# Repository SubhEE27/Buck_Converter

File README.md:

# LMR51450 Based Buck Converter (10–35 V → 7.6 V @ 4 A)

This project implements a **DC-DC Buck Converter** using the **Texas Instruments LMR51450** regulator IC.  
The design converts an input range of **10 V to 35 V** into a regulated **7.6 V output** at up to **4 A continuous current**.

The schematic, PCB layout, and BOM are included, designed in **KiCad**.

---

## 📐 Design Specifications
- Input Voltage Range: 10 – 35 V  
- Output Voltage: 7.6 V  
- Max Output Current: 4 A  
- Switching Frequency: ~500 kHz  
- Capacitor Type: X7R dielectric (temperature-stable, low ESR)  

---

## 🔧 Key Component Choices

- **Feedback Network**  
  - Output voltage set using divider resistors: ~90 kΩ (top), 10 kΩ (bottom).  

- **Switching Frequency**  
  - RT resistor: ~402 kΩ, corresponding to ~500 kHz operation.  

- **Inductor**  
  - Value: 4.7 µH  
  - Rated current: ≥ 7 A saturation, low DCR (<20 mΩ).  

- **Output Capacitor (COUT)**  
  - Requirement: ≥ 25 µF effective capacitance.  
  - Chosen: 2 × 22 µF, 16 V X7R ceramics → ~40 µF effective.  

- **Input Capacitor (CIN)**  
  - Requirement: rated ≥ 2 × VINmax (≥ 50 V).  
  - Chosen: 2 × 4.7 µF, 50 V X7R ceramics, plus 0.1 µF ceramic for high-frequency filtering.  

- **Bootstrap Capacitor (CBOOT)**  
  - 0.1 µF, 16 V X7R ceramic.  

- **Feedforward Capacitor (CFF)**  
  - ~15 pF, improves transient response and loop stability.  

---

## 🧾 BOM (Major Components)

| Reference | Value / Part         | Notes                               |
|-----------|----------------------|-------------------------------------|
| U1        | LMR51450             | Buck regulator IC                   |
| L1        | 4.7 µH, 7 A sat.     | Shielded power inductor             |
| CIN       | 2 × 4.7 µF, 50 V X7R | Input decoupling (low ESR)          |
| COUT      | 2 × 22 µF, 16 V X7R  | Output filter cap                   |
| CBOOT     | 0.1 µF, 16 V X7R     | Bootstrap capacitor                 |
| RFBT      | ~90 kΩ               | Feedback resistor (top)             |
| RFBB      | 10 kΩ                | Feedback resistor (bottom)          |
| CFF       | 15 pF                | Feedforward capacitor               |
| RT        | 402 kΩ               | Sets switching frequency            |

---

## 🖇️ Layout Guidelines
- Use a **solid ground plane** (bottom layer for 2-layer PCB).  
- Place **input capacitors (CIN)** as close as possible to VIN–PGND pins with direct vias.  
- Keep **SW node copper small** to reduce EMI.  
- Place **output capacitors (COUT)** close to the inductor and PGND return.  
- Stitch PGND and AGND together at a single point to minimize noise.  

---

## 📂 Repository Contents
- `/schematics/` → KiCad schematic files  
- `/pcb/` → PCB layout files  
- `/bom/` → Bill of Materials  
- `README.md` → This document  

---

## 📌 Notes
- All capacitors use **X7R dielectric** for thermal stability and low ESR.  
- Input capacitors are rated at least **2× the maximum VIN** for reliability.  
- Design optimized for **low ripple**, **high efficiency**, and **fast transient response**.

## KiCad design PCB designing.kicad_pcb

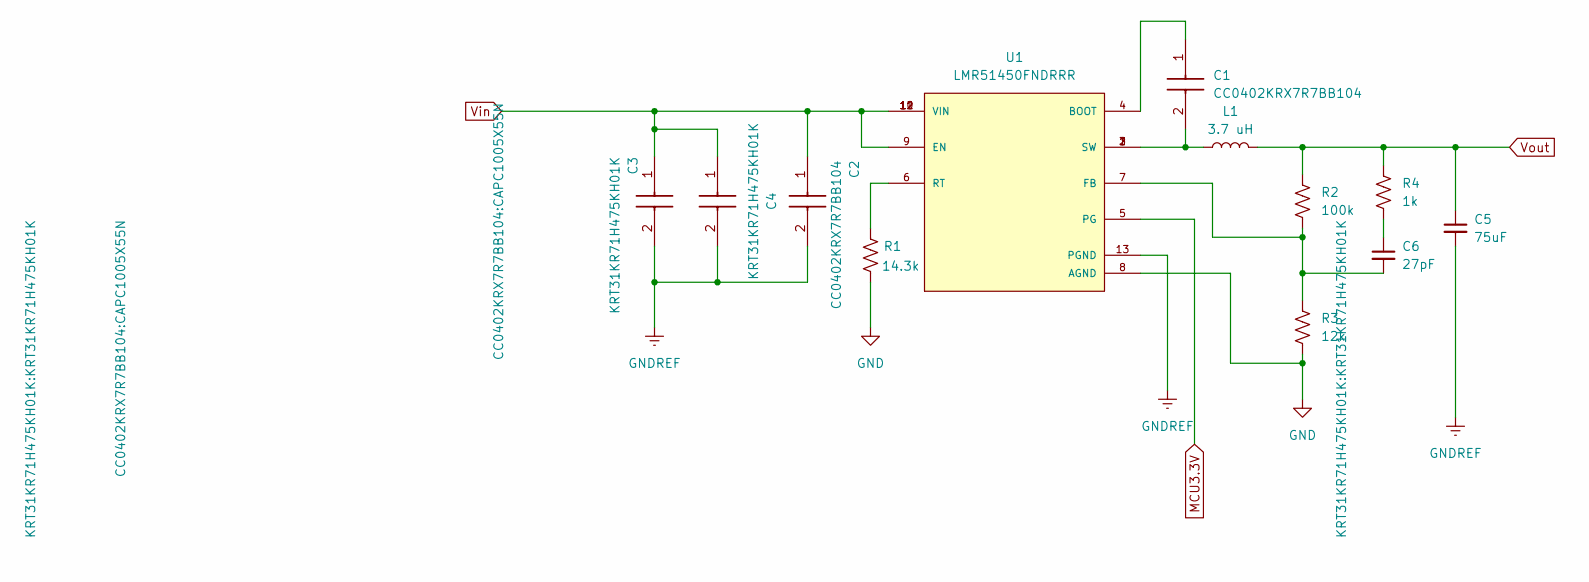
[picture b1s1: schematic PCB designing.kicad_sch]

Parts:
C1, C2: CC0402KRX7R7BB104; CAPC1005X55N; Mouser Part Number 603-CC402KRX7R7BB104
C3, C4: KRT31KR71H475KH01K; Manufacturer_Part_Number KRT31KR71H475KH01K
C5: 75uF; CP_Elec_5x5.4
C6: 27pF; CP_Elec_5x5.4
L1: 3.7 uH; L_Bourns-SRN8040_8x8.15mm
R1: 14.3k; R_0612_1632Metric
R2: 100k; R_0612_1632Metric
R3: 12k; R_0612_1632Metric
R4: 1k; R_0612_1632Metric
U1: LMR51450FNDRRR; CONV_LMR51450FNDRRR; PARTREV December 2022

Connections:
GND: R1.2, R3.2, U1.8 (AGND)
GNDREF: C2.2, C3.2, C4.2, C5.2, U1.13 (PGND)
MCU3.3V: U1.5 (PG)
unnamed: C1.2, L1.1, U1.1 (SW), U1.2 (SW), U1.3 (SW)
unnamed: C6.1, R4.2
unnamed: C1.1, U1.4 (BOOT)
unnamed: C6.2, R2.2, R3.1, U1.7 (FB)
unnamed: R1.1, U1.6 (RT)
Vin: C2.1, C3.1, C4.1, U1.9 (EN), U1.10 (VIN), U1.11 (VIN), U1.12 (VIN)
Vout: C5.1, L1.2, R2.1, R4.1

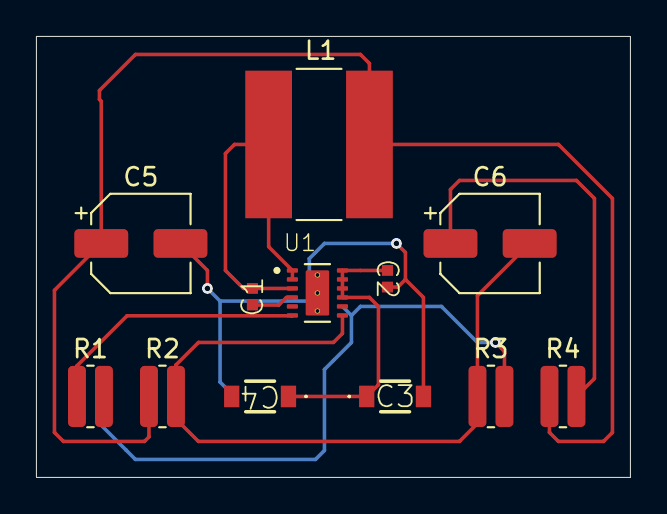
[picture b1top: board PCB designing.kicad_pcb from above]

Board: 2 copper layers, 33.0 x 24.5 mm, 12 parts (0 on the bottom side), 9 nets.

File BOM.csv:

"Id;""Designator"";""Footprint"";""Quantity"";""Designation"";""Supplier and ref"";",
"1;""U1"";""CONV_LMR51450FNDRRR"";1;""LMR51450FNDRRR"";;;",
"2;""C4","C3"";""KRT31KR71H475KH01K"";2;""KRT31KR71H475KH01K"";;;"
"3;""C2","C1"";""CAPC1005X55N"";2;""CC0402KRX7R7BB104"";;;"
"4;""R4"";""R_0612_1632Metric"";1;""1k"";;;",
"5;""R3"";""R_0612_1632Metric"";1;""12k"";;;",
"6;""R2"";""R_0612_1632Metric"";1;""100k"";;;",
"7;""R1"";""R_0612_1632Metric"";1;""14.3k"";;;",
"8;""L1"";""L_Bourns-SRN8040_8x8.15mm"";1;""3.7 uH"";;;",
"9;""C6"";""CP_Elec_5x5.4"";1;""27pF"";;;",
"10;""C5"";""CP_Elec_5x5.4"";1;""75uF"";;;",

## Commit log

2025-09-15 hdbhb.txt
2025-09-15 nh.txt
2025-09-15 README.md
2025-09-15 gvv.txt
